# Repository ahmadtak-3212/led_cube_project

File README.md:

# LED cube (formerly "galina")

A **4 × 4 × 4 RGB LED cube**, built twice:

- **V1:** the cube is driven straight from an **FPGA**. The SystemVerilog design scans the cube one LED at a time: it selects a column through a shift register, selects a layer, and applies 8-bit PWM to each colour channel.
- **V2:** the cube sits on a custom KiCad PCB carrying an **Arduino Nano (ATmega328P)**. It uses a charlieplexing library and a set of animations.

🎥 **Demo video:** [`docs/images/Galina_Results.mp4`](docs/images/Galina_Results.mp4). The video is 720p; GitHub shows a download or preview link for it.

<sub>V2 carrier PCB, rendered from <code>electrical/led_cube_pcb/GBR</code>.</sub>

## Status

| Area | Status |
|---|---|
| FPGA (V1) | ✅ Vivado project, testbenches and four prebuilt bitstreams |
| PCB (V2) | ✅ Routed; Gerbers exported, including a set prepared for a CNC etcher |
| Firmware (V2) | ✅ Animations running (see video) |
| Mechanical | ✅ PCB case, soldering jig, cut files |

## Repository layout

```
led_cube_project/
├── fpga/led_cube_v1/              Vivado project "Galina" (V1)
│   ├── Galina.xpr
│   ├── Galina.srcs/sources_1/new/ top_level.sv, led_driver_fsm.sv, write.sv, pwm.sv
│   ├── Galina.srcs/sources_1/ip/  clk_wiz_0 (clocking wizard)
│   ├── Galina.srcs/sim_1/         testbenches
│   ├── Galina.srcs/constrs_1/     .xdc constraints
│   ├── wcfg/                      saved waveform views for each testbench
│   └── runs/*.bit                 prebuilt bitstreams
├── electrical/led_cube_pcb/       KiCad 6 PCB for V2 (+ GBR/ Gerbers)
├── firmware/led_cube_firmware/    PlatformIO project for V2 (Arduino Nano)
├── mechanical/
│   ├── cad/                       SolidWorks: cube parts, Soldering_Jig.SLDASM
│   ├── cam/                       3D-print (.3mf), CNC-etcher Gerbers
│   └── exports/                   STL (PCB case + cover), SVG (laser-cut soldering jig)
└── docs/images/Galina_Results.mp4
```

## V1: FPGA driver (`fpga/led_cube_v1`)

**Target:** Xilinx Artix-7 **XC7A100T-CSG324** (`xc7a100tcsg324-3`), using the Nexys A7 / Nexys 4 DDR pinout. The 100 MHz clock is on pin E3, the cube connects through Pmod headers **JA** and **JB**, and `btnc`, `sw[15:0]` and `led[15:0]` come from the board.

**How it works:**

| Module | Role |
|---|---|
| `top_level.sv` | Holds the frame buffer `led_cube[4 layers][16 LEDs][24-bit RGB]` and a demo pattern generator. With `sw[0]` on, the cube cycles through white, red, green and blue every 4,000,000 clocks; `btnc` resets it. The board LEDs mirror the switches. |
| `led_driver_fsm.sv` | The scan FSM. For each LED in the current layer, it writes a one-hot 16-bit column pattern into the shift register and then runs a PWM slot for that pixel's RGB value. Each layer gets `MAX_CYCELS_PER_PLANE = 20833` clocks (16 slots of about 1302 clocks), after which it advances `z_level`. |
| `write.sv` | Shifts 16 bits out to a serial-in, parallel-out shift register chain. It drives SER, SRCLK and SRCLR, then pulses the latch. |
| `pwm.sv` | 8-bit PWM of the pixel's R, G and B bytes within one slot |
| `clk_wiz_0` | Divides the 100 MHz board clock down for the driver |

**Pmod pinout:**

| Pmod pin | Signal |
|---|---|
| `ja[0]` | shift-register serial data (SER) |
| `ja[1]` | shift clock (SRCLK) |
| `ja[2]` | shift-register clear (SRCLR, active low) |
| `ja[3]` | latch (RCLK) |
| `ja[4]`, `ja[5]`, `ja[6]` | red, green, blue PWM |
| `jb[3:0]` | one-hot layer select (z = 0…3) |

**Bitstreams** in `runs/` are `Brightness.bit`, `Checker.bit`, `EitherSide.bit` and `Full_Cube_Flash.bit`. Each is a different demo pattern.

**Rebuild or program:**
1. Open `Galina.xpr` in Vivado. The project was saved with **Vivado 2019.2**; newer versions will offer to upgrade it and the `clk_wiz_0` IP.
2. Run synthesis, implementation and bitstream generation.
3. Use Hardware Manager to program the board, or load one of the prebuilt `.bit` files.
4. To simulate, open any testbench in `sim_1` with its matching `.wcfg` from `wcfg/`.

## V2: Arduino carrier PCB (`electrical/led_cube_pcb`)

- KiCad 6, 2 layers, 111 × 98 mm.
- An **Arduino Nano v3** socket, sixteen **2 × 2 headers** (`J0,0` to `J3,3`, one per cube column, 4 leads each), and a 2-pin screw terminal for power.
- Gerbers are in `GBR/`. A copy set up for the desktop CNC etcher is in `mechanical/cam/CNC_Etcher/`.

## V2: firmware (`firmware/led_cube_firmware`)

| Setting | Value |
|---|---|
| Platform | `atmelavr`, board `nanoatmega328new` (Nano with the new bootloader), Arduino framework |
| Sources | `src/Firmware.ino` (animation loop), `src/cubeplex.h` (charlieplexing driver), `src/mappings.h` (pin-to-LED map), `src/niceTimer.h` |

The animations are `randomLed`, `planarSpin`, `fountian`, `trifade`, `shiftSquares`, `tunnel`, `chaseTheDot` and `planarFlop3D`.

```bash
cd firmware/led_cube_firmware
pio run -t upload          # Nano over USB
```

`platformio.ini` also points `lib_extra_dirs` at `~/Documents/Arduino/libraries`. The project doesn't need anything from there, because everything is in `src/`.

> **Credit:** `cubeplex.h`, `mappings.h`, `niceTimer.h` and the animation code in `Firmware.ino` come from **Asher Glick's** charlieplexed RGB cube library (Copyright © 2012 Asher Glick, BSD license; the full text is in `src/LICENCE` and in each file header). My work in V2 is the PCB, the build and the integration.

## Mechanical

| File | What |
|---|---|
| `cad/Soldering_Jig/Soldering_Jig.SLDASM` + `exports/svg/Soldering_Jig/*.svg` | Laser-cut jig that holds LEDs in a 4 × 4 grid while soldering each layer |
| `exports/stl/Galina_PCB_Case.STL`, `Galina_PCB_Cover.STL` | 3D-printed enclosure for the V2 PCB (`cam/3D_Printer/Galina_PCB_Casse.3mf` is the print project) |
| `cad/Galina/Parts/` | Cube part models |

## Reproducing

1. Laser-cut the soldering jig from the SVGs, then solder four 4 × 4 layers of common-lead RGB LEDs and stack them into columns.
2. **V2:** mill or order the PCB from `GBR/`, fit a Nano, plug each column into its 2 × 2 header, and flash the firmware.
3. **V1:** wire the Pmod pins as in the table above to a 16-bit shift-register column driver and four layer drivers, then program a bitstream.

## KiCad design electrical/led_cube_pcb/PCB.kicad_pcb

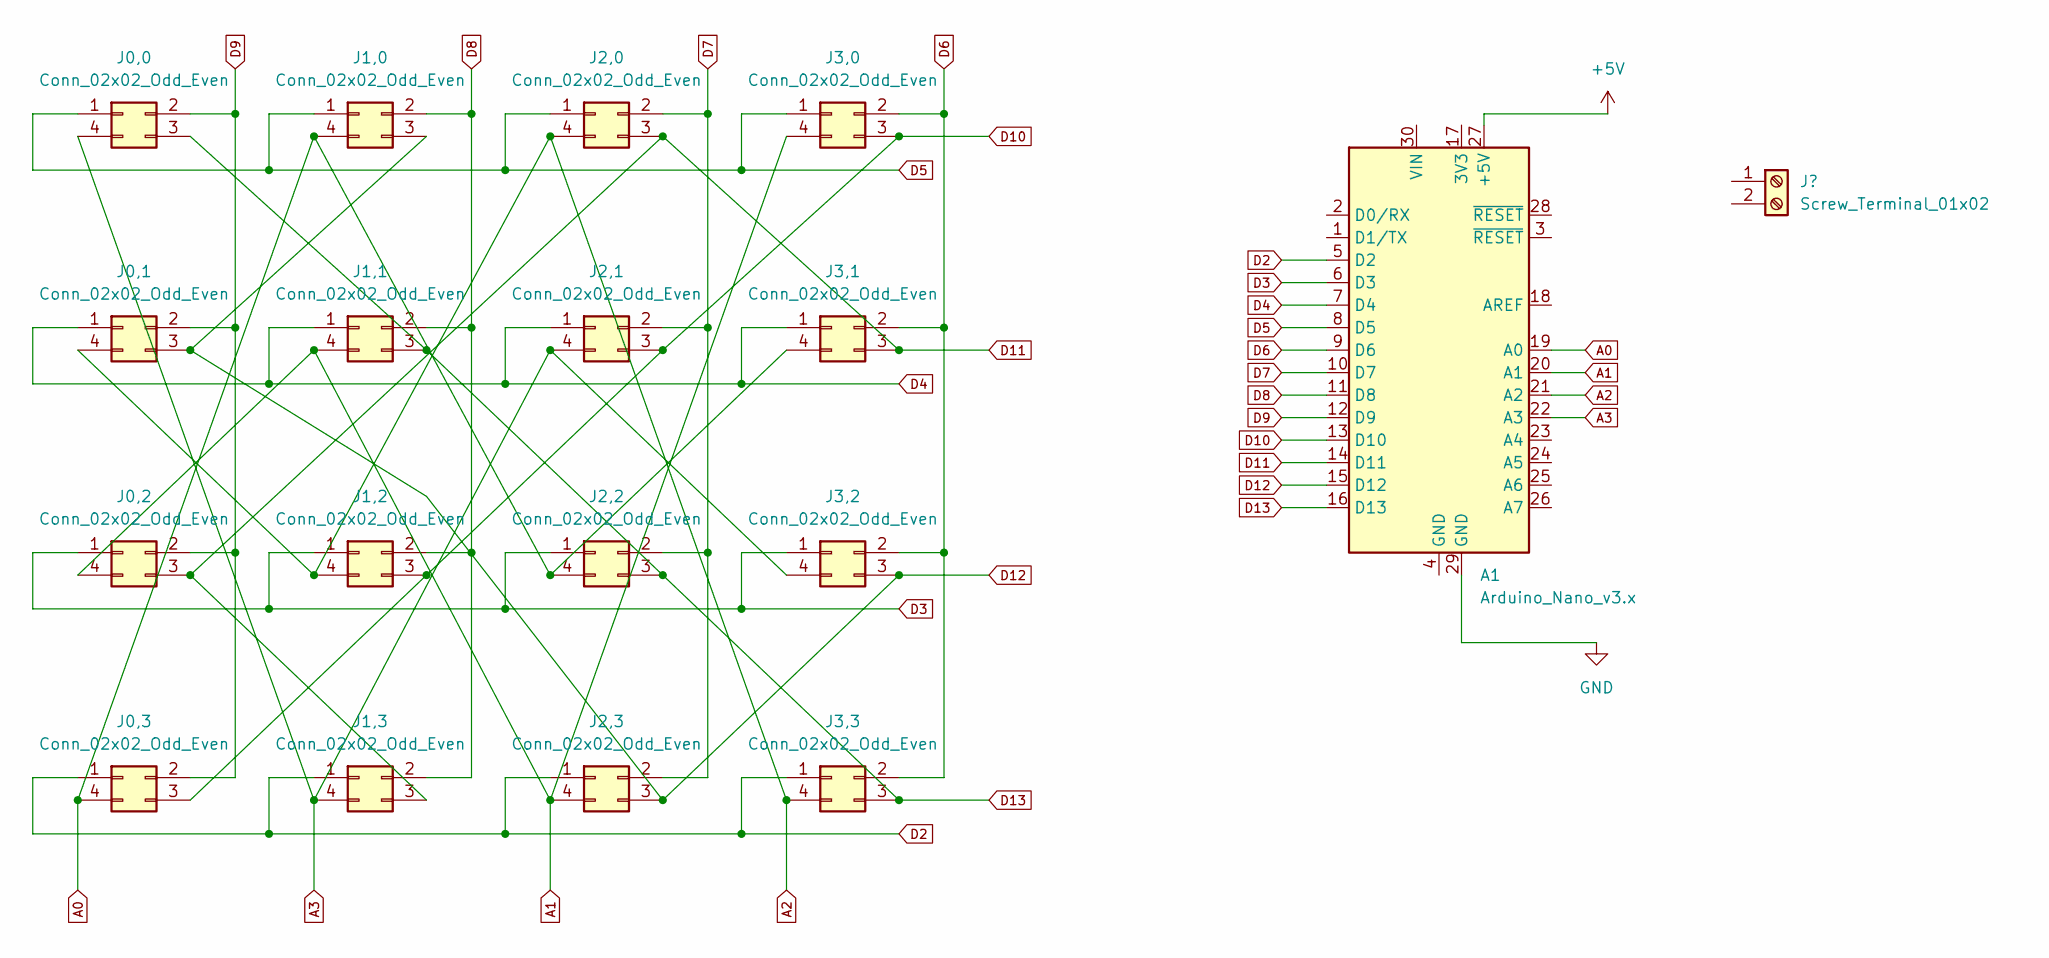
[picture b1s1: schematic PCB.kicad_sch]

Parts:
A1: Arduino_Nano_v3.x; Arduino_Nano
J0,0: Conn_02x02_Odd_Even
J0,1, J0,2, J0,3, J1,0, J1,1, J1,2, J1,3, J2,0, J2,1, J2,2, J2,3, J3,0, J3,1, J3,2, J3,3: Conn_02x02_Odd_Even; LED_D5.0mm-4_RGB_Square

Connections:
+5V: A1.27 (+5V)
A0: A1.19 (A0), J0,3.4, J1,0.4, J2,2.4, J3,1.4
A1: A1.20 (A1), J0,2.4, J1,1.4, J2,3.4, J3,0.4
A2: A1.21 (A2), J0,1.4, J1,2.4, J2,0.4, J3,3.4
A3: A1.22 (A3), J0,0.4, J1,3.4, J2,1.4, J3,2.4
D2: A1.5 (D2), J0,3.1, J1,3.1, J2,3.1, J3,3.1
D3: A1.6 (D3), J0,2.1, J1,2.1, J2,2.1, J3,2.1
D4: A1.7 (D4), J0,1.1, J1,1.1, J2,1.1, J3,1.1
D5: A1.8 (D5), J0,0.1, J1,0.1, J2,0.1, J3,0.1
D6: A1.9 (D6), J3,0.2, J3,1.2, J3,2.2, J3,3.2
D7: A1.10 (D7), J2,0.2, J2,1.2, J2,2.2, J2,3.2
D8: A1.11 (D8), J1,0.2, J1,1.2, J1,2.2, J1,3.2
D9: A1.12 (D9), J0,0.2, J0,1.2, J0,2.2, J0,3.2
D10: A1.13 (D10), J0,3.3, J1,2.3, J2,1.3, J3,0.3
D11: A1.14 (D11), J0,2.3, J1,3.3, J2,0.3, J3,1.3
D12: A1.15 (D12), J0,1.3, J1,0.3, J2,3.3, J3,2.3
D13: A1.16 (D13), J0,0.3, J1,1.3, J2,2.3, J3,3.3
GND: A1.29 (GND)

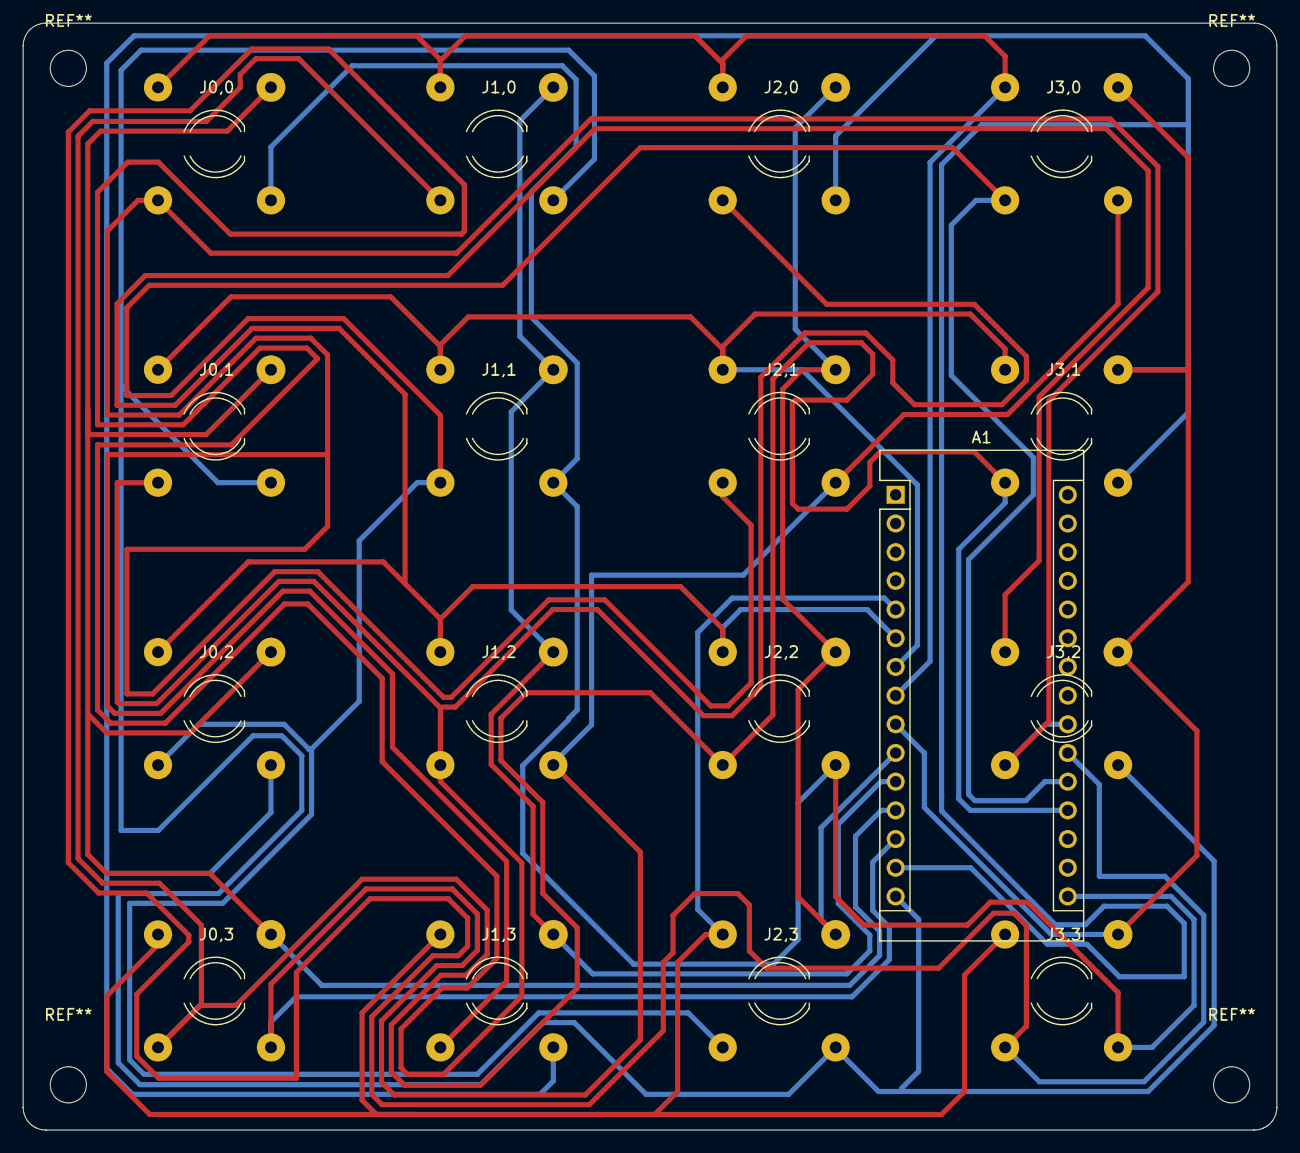
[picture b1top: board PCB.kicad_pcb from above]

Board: 2 copper layers, 111.0 x 98.0 mm, 17 parts (0 on the bottom side), 16 nets.
